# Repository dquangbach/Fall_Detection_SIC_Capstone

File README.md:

# Fall Detection — CNN-LSTM & Leave-One-Subject-Out

Dự án phát hiện té ngã từ gia tốc ba trục, sử dụng **CNN-LSTM** và đánh giá khả năng tổng quát hóa sang người chưa xuất hiện trong tập train bằng **Leave-One-Subject-Out (LOSO)** trên **32 subject K-Fall**.

Pipeline chính nằm trong [model_cnn_lstm_loso.ipynb](model_cnn_lstm_loso.ipynb): đọc nhãn K-Fall, tạo cửa sổ, huấn luyện và đánh giá 32 fold, sau đó train model cuối trên dữ liệu của cả 32 subject. [model_cnn_lstm.ipynb](model_cnn_lstm.ipynb) là thử nghiệm đối chứng với split cố định và **không augmentation**; không phải nguồn kết quả LOSO.

Repository còn có thiết kế PCB, phần firmware ESP32-S3/MPU6050 và receiver Polar H10 phục vụ thử nghiệm. Model CNN-LSTM Keras hiện tại và model nhúng trong firmware là các bộ artifact khác nhau.

## Cấu trúc dự án

```text
.
├── model_cnn_lstm_loso.ipynb     # Pipeline chính: LOSO + train model cuối
├── model_cnn_lstm.ipynb          # Đối chứng: split subject cố định, no augmentation
├── saved_models_cnn_lstm/
│   ├── best_model_SAxx.keras    # Checkpoint của fold có SAxx làm test
│   ├── final_selection_best.keras
│   ├── final_model.keras       # Model train lại trên toàn bộ 32 subject
│   ├── scaler.pkl              # Scaler đi cùng final_model.keras
│   ├── metadata.pkl            # Features, window, threshold, thông tin train cuối
│   ├── best_model_noaug.keras  # Checkpoint thử nghiệm no augmentation
│   └── best_model.keras        # Checkpoint thử nghiệm trước đó
├── kfall/
│   ├── label_data_new/         # Nhãn onset/impact: SAxx_label.xlsx
│   └── sensor_data_new/        # CSV theo subject, chuẩn bị riêng ở máy local
├── polar_h10_receiver/         # Thử nghiệm inference Python từ UDP Polar H10
├── esp32s3-tinyml-fall-detector/ # Repository firmware được ghi nhận bằng gitlink
├── fall_detection_pcb/         # Schematic, PCB, footprint KiCad và PDF
├── fall_detection_dataset/     # Dữ liệu local của pipeline cũ
└── doc/                        # Tài liệu tham khảo local
```

Các notebook cũ như `model.ipynb` và `model_3_features.ipynb` không còn trong cây dự án hiện tại. Bắt đầu với **`model_cnn_lstm_loso.ipynb`**.

## Dữ liệu và nhãn

Notebook chính đọc trực tiếp:

```text
kfall/
├── label_data_new/
│   ├── SA06_label.xlsx
│   └── ...
└── sensor_data_new/
    ├── SA06/
    │   ├── S06T01R01.csv
    │   └── ...
    └── ...
```

- Danh sách subject được lấy từ các thư mục bắt đầu bằng `SA` trong `sensor_data_new`.
- Tên CSV theo mẫu `SxxTxxRxx.csv`, chứa subject, task và trial.
- CSV cần các cột `FrameCounter`, `AccX`, `AccY`, `AccZ`. Dữ liệu được dùng theo thứ tự dòng có sẵn trong file; cần giữ thứ tự thời gian.
- File Excel nhãn sử dụng `Task Code (Task ID)`, `Trial ID`, `Fall_onset_frame`, `Fall_impact_frame`.
- Nhãn mẫu là ngã nếu `onset <= FrameCounter <= impact`. Recording không có trong bảng nhãn được xem là bình thường; cần chuẩn bị đầy đủ các file nhãn để tránh gán sai.
- Pipeline này không cần cột `FallCheck` và không đọc từ `Sample_Training/Sample_Test` của pipeline cũ.

Dữ liệu gia tốc dùng đơn vị **g**, với bước thời gian 0.01 giây (100 Hz) trong CSV K-Fall hiện có. Notebook không tự resample hoặc chuyển đơn vị.

### Cửa sổ và chuẩn hóa

| Thiết lập | Giá trị |
|---|---|
| Features theo thứ tự | `AccX, AccY, AccZ` |
| Window size | 200 mẫu, khoảng 2 giây ở 100 Hz |
| Window step | 100 mẫu, overlap 50% |
| Nhãn cửa sổ | Fall nếu ít nhất 20% mẫu nằm trong khoảng onset–impact |
| Input model | `(batch, 200, 3)`, không flatten |
| Output | Một sigmoid score cho lớp Fall |
| Decision threshold | `score >= 0.50` → Fall |

Cửa sổ được tạo riêng trong từng recording; không nối hai recording hoặc hai subject. Đoạn cuối thiếu 200 mẫu bị bỏ qua. Cửa sổ từng subject được cache trong RAM để tái sử dụng qua các fold.

Trong mỗi fold, `StandardScaler` được fit **chỉ trên cửa sổ train gốc**, theo từng feature bằng `reshape(-1, 3)`. Scaler đó transform train, train augmentation, validation và test. Không fit scaler trên subject test.

### Augmentation của pipeline chính

Chỉ áp dụng lên tập train, trước chuẩn hóa:

| Phép biến đổi | Xác suất trên mỗi bản sao cửa sổ | Cấu hình |
|---|---:|---|
| Jitter | 0.10 | Nhiễu Gaussian, mean 0, sigma 0.05 |
| Scaling | 0.10 | Một hệ số chung cho Acc XYZ, Gaussian mean 1, sigma 0.10 |
| Rotation | 0.10 | Góc ngẫu nhiên ±10° mỗi trục, cùng phép quay cho toàn bộ cửa sổ |

Ba phép được chọn độc lập nên một cửa sổ có thể nhận nhiều phép hoặc không nhận phép nào. Ghép tập gốc với tập bản sao để tăng gấp đôi số window train; nhãn giữ nguyên. Validation/test của LOSO không augmentation.

## Kiến trúc CNN-LSTM

```text
Input (200, 3)
  → Conv1D(32, kernel=5, same) → BatchNorm → ReLU → MaxPool(2) → Dropout(0.2)
  → Conv1D(64, kernel=3, same) → BatchNorm → ReLU → MaxPool(2) → Dropout(0.2)
  → LSTM(64, dropout=0.2, recurrent_dropout=0)
  → Dense(32, ReLU) → Dropout(0.3)
  → Dense(1, sigmoid)
```

CNN trích đặc trưng cục bộ theo thời gian; LSTM xử lý chuỗi đặc trưng sau hai bước pooling. Loss là `binary_crossentropy`; optimizer Adam bắt đầu tại learning rate `1e-3`. Class weight được tính theo `N / (2 × N_class)` để cân bằng hai lớp.

## Đánh giá Leave-One-Subject-Out

Với 32 subject, notebook chạy 32 fold. Trong mỗi fold:

1. Giữ 1 subject làm **test độc lập**.
2. Chọn xoay vòng 2 subject trong 31 subject còn lại làm validation.
3. Dùng 29 subject còn lại để train, augmentation và fit scaler.
4. Khởi tạo CNN-LSTM mới, chọn checkpoint theo validation.
5. Nạp checkpoint tốt nhất và dự đoán subject test tại threshold cố định 0.50.

Mỗi subject làm test đúng một lần. Đây là LOSO có validation tách theo subject, không phải chia ngẫu nhiên window và cũng không phải nested LOSO để tìm hyperparameter.

### Cấu hình huấn luyện mỗi fold

| Thiết lập | Giá trị trong code |
|---|---|
| Batch size | 32 |
| Epoch tối đa | 50 |
| ModelCheckpoint | `val_recall`, `mode="max"`, lưu best |
| EarlyStopping | `val_recall`, patience 12, min_delta `1e-3`, restore best weights |
| ReduceLROnPlateau | `val_loss`, patience 3, factor 0.5, min_lr `1e-5` |
| Threshold test | 0.50, không quét ngưỡng trên test |

Checkpoint lưu thành `saved_models_cnn_lstm/best_model_<test_subject>.keras`. Test dùng checkpoint tải lại; `ModelCheckpoint` không đặt `min_delta` như `EarlyStopping`, nên hai callback có thể chọn epoch khác nhau.

### Báo cáo kết quả

Cell tổng hợp tạo:

- Bảng mỗi fold: số window, phân bố lớp, Accuracy, Precision/Recall/F1/F2 lớp Fall, ROC-AUC và TN/FP/FN/TP.
- Mean, standard deviation, min và max qua các fold. ROC-AUC là NaN nếu test fold chỉ có một lớp.
- Confusion matrix và classification report gộp dự đoán của toàn bộ subject test.
- Biểu đồ Precision và Recall theo subject.

Mean qua subject và metrics gộp theo window là hai cách tổng hợp khác nhau. Các chỉ số ở đây đánh giá **cửa sổ**, không tự tương đương số sự kiện ngã phát hiện được hoặc số cảnh báo giả mỗi giờ.

**Tình trạng kết quả trong repository:** có 32 checkpoint theo subject, nhưng notebook LOSO hiện lưu với output rỗng và chưa có bảng metrics LOSO được export. Vì vậy README không gán số đo từ notebook đối chứng hay validation của model cuối cho LOSO. Để công bố kết quả, lưu output cell tổng hợp và bảng từng fold sau lần chạy tương ứng.

Scalers từng fold và dự đoán test chưa được lưu thành artifact riêng. Cell mục 7 có thể nạp trực tiếp 32 file `best_model_SAxx.keras` và dựng lại scaler từ đúng 29 subject train gốc của mỗi fold, không cần train lại model. Việc này yêu cầu giữ nguyên dataset, nhãn, thứ tự subject, features, window và cách chia fold như khi train checkpoint. `scaler.pkl` hiện có thuộc model cuối; không dùng scaler này để đánh giá checkpoint LOSO.

## Train model cuối trên 32 subject

Cell cuối của notebook chính dùng `FINAL_USE_AUGMENTATION = True`, seed 42 và thực hiện hai pha:

1. **Chọn epoch:** ghép dữ liệu 32 subject, fit scaler trên toàn bộ window gốc, tạo augmentation, chuẩn hóa và shuffle. Giữ 10% window bằng `validation_split=0.10`; train tối đa 100 epoch, với checkpoint/early stopping theo `val_recall` (patience 12) và giảm LR theo `val_loss` (patience 3). Chọn `argmax(val_recall) + 1`.
2. **Train lại toàn bộ:** khởi tạo CNN-LSTM mới và train trên tất cả window gốc + augmentation của 32 subject đến epoch vừa chọn. Pha này không giữ validation, không dùng early stopping hoặc ReduceLROnPlateau; Adam bắt đầu lại tại `1e-3`. Lưu thành `final_model.keras`.

Validation pha 1 là split theo window sau khi augmentation và fit scaler toàn bộ; các window overlap hoặc bản gốc/bản sao có thể nằm hai phía của split. Vì vậy nó chỉ là tín hiệu chọn epoch nội bộ, **không phải đánh giá subject độc lập**. Lịch giảm LR ở pha 1 cũng không được phát lại trong pha train toàn bộ. Chất lượng cần được báo cáo bằng protocol đánh giá phù hợp, không bằng training score của model cuối.

File `metadata.pkl` hiện ghi: **32 subject, augmentation bật, selected_epoch = 13**, `selected_val_recall ≈ 0.996633`. Đây là thông tin pha chọn epoch của lần export, không phải Recall LOSO hay kết quả kiểm thử độc lập của `final_model.keras`.

### Bộ artifact để inference

| File trong `saved_models_cnn_lstm/` | Vai trò |
|---|---|
| `final_model.keras` | CNN-LSTM train lại trên toàn bộ dữ liệu |
| `scaler.pkl` | StandardScaler fit trên window gốc của 32 subject |
| `metadata.pkl` | Feature order, window size/step, threshold, subject và cấu hình train cuối |
| `final_selection_best.keras` | Checkpoint pha chọn epoch; không phải model train lại toàn bộ |
| `best_model_SAxx.keras` | Model fold LOSO có subject SAxx làm test |
| `best_model_noaug.keras` | Checkpoint thử nghiệm đối chứng no augmentation |

Luôn sử dụng `final_model.keras`, `scaler.pkl` và `metadata.pkl` từ cùng lần export. Khi inference, chỉ transform bằng scaler đã lưu; không fit lại scaler, không augmentation.

## Cài đặt và chạy

Từ thư mục gốc repository:

```bash
python3 -m venv .venv
source .venv/bin/activate
python -m pip install tensorflow numpy pandas scikit-learn matplotlib joblib openpyxl jupyterlab
python -m jupyter lab
```

Trên Windows, kích hoạt bằng `.venv\Scripts\activate`. Chưa có file khóa dependency Python trong repository; cần lưu phiên bản môi trường cho các lần chạy cần tái lập.

1. Chuẩn bị đầy đủ CSV và Excel nhãn theo cấu trúc `kfall/` ở trên.
2. Mở `model_cnn_lstm_loso.ipynb`, chọn kernel đúng môi trường, chạy với working directory là gốc repository.
3. Chạy các cell import, đọc nhãn, cấu hình, cache dữ liệu, augmentation và định nghĩa model.
4. Nếu đã có 32 checkpoint, chạy thẳng **mục 7** để nạp model và đánh giá; chỉ cần import và các mục 1–3, bỏ qua mục 6. Nếu cần train lại, chạy mục 6 trước. Lưu notebook cùng output khi cần báo cáo.
5. Sau khi chốt cách đánh giá, chạy cell cuối để tạo model cho toàn bộ 32 subject.

Nếu chỉ cần train model cuối sau khi đã hoàn tất LOSO, có thể chạy các cell chuẩn bị ở bước 3 rồi chuyển thẳng đến cell cuối; không bắt buộc chạy lại 32 fold. Chạy lại sẽ ghi đè các artifact cùng tên trong `saved_models_cnn_lstm/`; sao lưu bộ cần giữ trước khi thực hiện.

LOSO hiện không đặt seed riêng cho từng fold, trong khi cell final đặt seed 42. Các lần chạy LOSO có thể khác nhau do khởi tạo trọng số, dropout và augmentation ngẫu nhiên.

### Notebook đối chứng

`model_cnn_lstm.ipynb` giữ 6 subject test cố định:
`SA21, SA23, SA24, SA26, SA30, SA33`; chia 26 subject còn lại thành 21 train và 5 validation. Cấu hình hiện tại không augmentation, tối đa 100 epoch, early stopping patience 12 và LR patience 3. Kết quả của notebook này phục vụ đối chiếu, không thay thế đánh giá LOSO.

## Thử nghiệm trực tiếp với Polar H10

Khi có thư mục `polar_h10_receiver/`, chạy trong môi trường đã cài dependencies:

```bash
python polar_h10_receiver/udp_acc_receiver.py --check-model
python polar_h10_receiver/udp_acc_receiver.py
```

Sender gửi UDP đến IP máy tính, port **5005**, theo `timestamp,x_mg,y_mg,z_mg`, với tốc độ đã cấu hình **100 mẫu/giây**. Receiver:

- Đổi mg → g và đổi trục thành `(Polar Y, -Polar X, -Polar Z)`.
- Gom window 200 mẫu, dự đoán lại mỗi 100 mẫu, dùng bộ artifact final.
- In sigmoid score và nhãn tại threshold trong metadata.
- Bỏ mẫu lỗi/trùng/đảo timestamp; reset sau 2 giây không nhận mẫu hợp lệ.

Mặc định đếm frame ở 100 Hz, không resample. Khi biết đơn vị timestamp, có thể thêm `--timestamp-unit ns` (hoặc `us/ms`) để kiểm tra nhịp lấy mẫu và khoảng mất mẫu. Thêm `--show-acc` để xem gia tốc.

Mapping trục giữ từ thử nghiệm receiver; hướng gắn cảm biến, dấu trục Z và khác biệt vị trí đo so với K-Fall cần được xác nhận thực nghiệm. Kết quả LOSO trên K-Fall không tự đại diện cho chất lượng nhận diện trực tiếp trên Polar.

## Phần cứng và trạng thái triển khai

- `fall_detection_pcb/`: thiết kế KiCad, schematic, PCB, footprint ESP32-S3/header và các PDF lớp mạch.
- `esp32s3-tinyml-fall-detector/`: phần firmware ESP32-S3 + MPU6050, lấy mẫu, preprocessing, TFLite Micro, LED và Wi-Fi/MQTT.

Firmware đang là repository riêng, được repository này tham chiếu bằng gitlink; hiện chưa có `.gitmodules` để tự khởi tạo bằng `git submodule update`. Khi clone mới, cần lấy firmware từ repository riêng và đối chiếu revision được ghi nhận.

Bản firmware local đang có thay đổi chưa commit cho input INT8 6 features `(200 × 6)`, step 50; revision firmware được repository chính tham chiếu vẫn dùng cấu hình 8 features. Cả hai đều khác bộ CNN-LSTM final với input float32 `(1,200,3)`. Chưa có artifact TFLite/C của CNN-LSTM final trong `saved_models_cnn_lstm/`; cần thực hiện export, đồng bộ preprocessing và kiểm tra runtime trước khi triển khai model này lên ESP32-S3.

## Dữ liệu và quản lý repository

CSV và file H5 bị loại theo `.gitignore`; thư mục sensor K-Fall cần chuẩn bị riêng khi clone. Các Excel nhãn K-Fall và bộ checkpoint Keras hiện được Git theo dõi. `doc/`, môi trường ảo và cache Python là dữ liệu local.

Thêm một thư mục vào `.gitignore` không tự bỏ tracking các file đã commit. Receiver Polar hiện vẫn có file được Git theo dõi; cần phân biệt tình trạng đó với quy tắc ignore local.

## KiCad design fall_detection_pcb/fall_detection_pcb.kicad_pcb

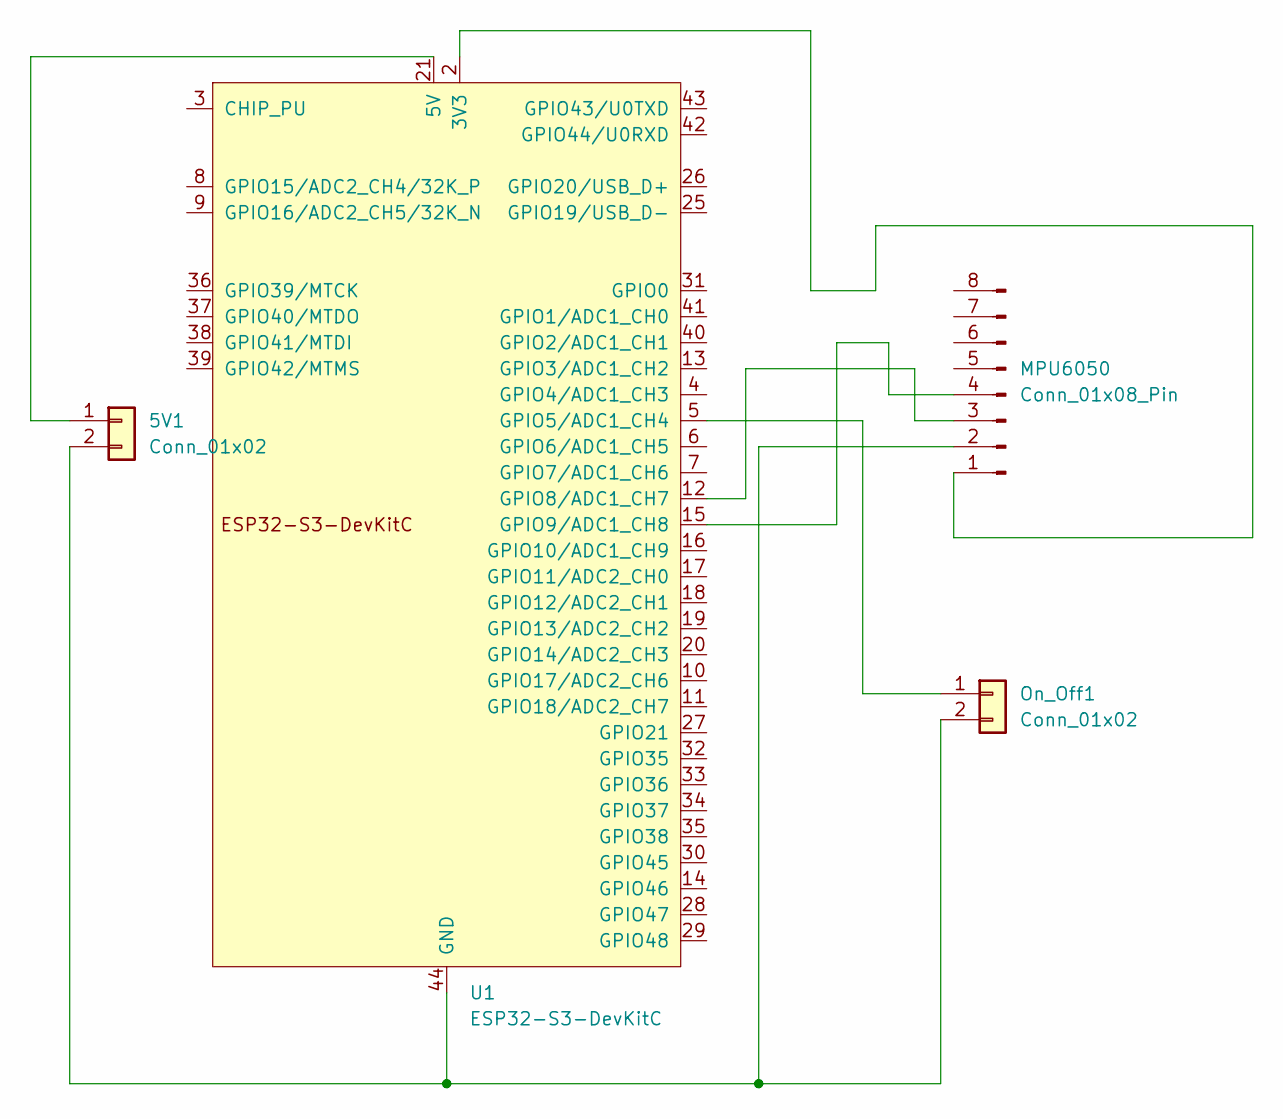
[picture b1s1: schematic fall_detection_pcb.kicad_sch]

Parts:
5V1: Conn_01x02; PinHeader_1x02_P2.54mm_Vertical
MPU6050: Conn_01x08_Pin; PinHeader_1x08_P2.54mm_Horizontal
On_Off1: Conn_01x02; PinHeader_1x02_P2.54mm_Vertical
U1: ESP32-S3-DevKitC

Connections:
unnamed: 5V1.1, U1.21 (5V)
unnamed: 5V1.2, MPU6050.2, On_Off1.2, U1.22 (GND), U1.23 (GND), U1.24 (GND), U1.44 (GND)
unnamed: MPU6050.1, U1.1 (3V3), U1.2 (3V3)
unnamed: MPU6050.3, U1.12 (GPIO8/ADC1_CH7)
unnamed: MPU6050.4, U1.15 (GPIO9/ADC1_CH8)
unnamed: On_Off1.1, U1.5 (GPIO5/ADC1_CH4)

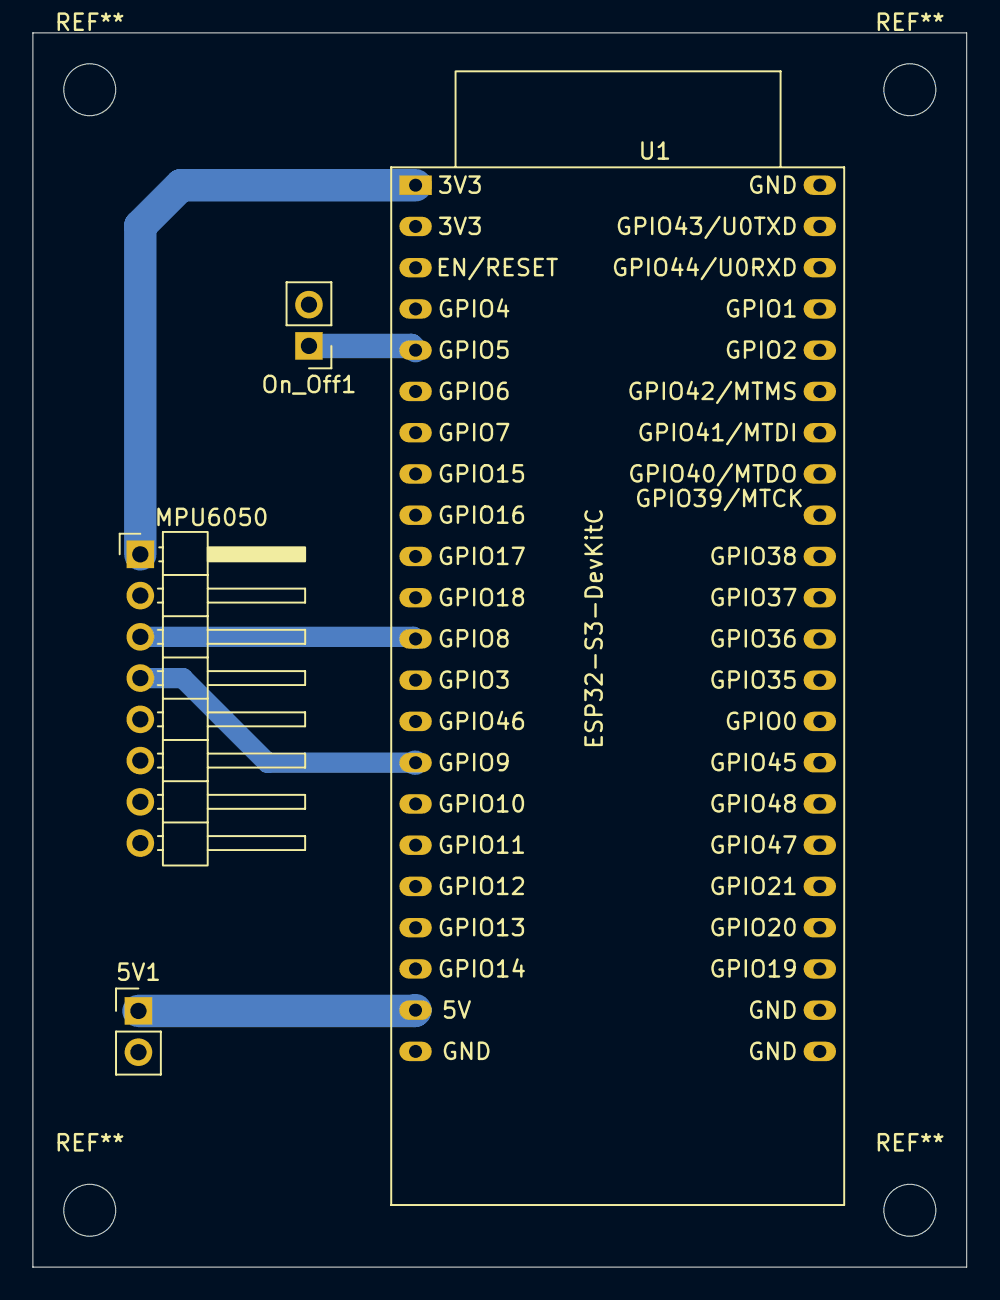
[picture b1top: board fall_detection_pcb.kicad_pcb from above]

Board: 2 copper layers, 57.5 x 76.0 mm, 4 parts (0 on the bottom side), 6 nets.
